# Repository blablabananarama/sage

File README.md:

# Bayleaf: ultra-low-profile wireless split keyboard (reproduction)

This is an open, buildable re-creation of Sebastian Graz's [Bayleaf](https://www.graz.io/articles/bayleaf-wireless-keyboard/): a 60-key (2 × 5×6) ortholinear split keyboard. It uses Kailh PG1316S laptop-style switches, runs ZMK on nice!nano controllers, and sits in a CNC-machined aluminium case 5 mm thick.

> **Provenance.** The original Bayleaf is a one-off prototype and is **not open source**. None of its files are used here. This repository is an independent design built to the published specs (139 × 93 mm per half, 5 mm thick, ~180 g, PG1316S, nice!nano/ZMK, CNC aluminium enclosure, MJF keycaps). Everything else was designed from scratch: board layout, pin mapping, case geometry, keymap and part choices. The PG1316S land pattern comes from Kailh's datasheet (CPG1316S01D02).

| | |
|---|---|
|  |  |
|  |  |
|  |  |
|  | |
|  |  |

**[Interactive case viewer](https://claude.ai/artifact/CuZ9wQ9LTKb2B2hHYhkEA2)**: rotate the five case versions, switch between them and try finishes (source: `docs/viewer/index.html`).

*Renders are generated from the actual STEP files and the routed PCB artwork (`docs/render3d/render.sh`). The case follows the original's MK5 drawing for the plan view and, for the top surface, the shape drawn in the [case sketchpad](https://claude.ai/artifact/11zAxZXfv3bXQXGKN8ovCU) ([data](docs/case-sketchpad-shape.json)): a one-piece silver shell with two flat levels, a 3.2 mm rim around the keys and a 5.0 mm plateau over the controller, joined by soft S-bends, plus a screwed-on black FR4 bottom plate.*

| | Original Bayleaf (published) | This reproduction |
|---|---|---|
| Layout | 60 % ortholinear split | 2 × 5 rows × 6 columns, 17 × 17 mm pitch |
| Size per half | 139 × 93 mm; "tallest part is only 5 mm" | 139.4 × 96.8 mm base. 3.2 mm rim around the keys; 5.0 mm plateau over the controller |
| Weight | 180 g | ~165 g estimated (15 g aluminium shell + 17 g FR4 plate per half) |
| Switches | Kailh PG1316S | Kailh PG1316S, soldered from below with an iron: contacts through castellated half-holes, frame anchors through plated holes (a hotplate is optional) |
| Keycaps | custom MJF prints | stock Kailh PG1316S 1U caps (16 × 16 mm) |
| Controller | nice!nano, ZMK | nice!nano v2 soldered flush, ZMK (BLE split) |
| Battery | "over a month" | 302030 LiPo (~120–150 mAh) per half, deep sleep after 15 min |
| Case | CNC aluminium, raised over the controller | One-piece CNC 6061 shell (key window, roofed controller bay, 7 tapped M2 posts) + 0.8 mm FR4 bottom plate (a copper-free PCB, so the radio gets out) ([notes](docs/case-drawing.md)) |

## What's in here

```
hardware/pcb/generate_pcb.py      the whole PCB as code: placement, nets, outline -> Freerouting -> DRC -> fab files;
                                  also the FR4 bottom plates
hardware/pcb/bayleaf-{left,right}.kicad_pcb   routed KiCad 7 boards (open in KiCad to inspect or edit)
hardware/pcb/lib/bayleaf.pretty/  footprints: PG1316S (castellated, hand-solderable), nice!nano (flush), battery pads
hardware/pcb/fab/{left,right}/    gerbers+drill zip, JLCPCB BOM/CPL, 3D STEP of the board, DRC report
hardware/pcb/fab/plate-{left,right}/  gerbers+drill zip of the FR4 bottom plates
hardware/case/case.py             parametric shell (drafted or straight + chamfer) (CadQuery); out/ has STEP + STL (plate too, for reference)
firmware/                         ZMK shield "bayleaf" + keymap; built by .github/workflows/firmware.yml
docs/BOM.csv                      full bill of materials with prices
docs/ordering.md                  exact fab settings (PCB, PCBA, CNC, parts)
docs/shopping-list.md             every part to buy, with shop links
docs/assembly.md                  step-by-step build guide
docs/schematic.md                 circuit / pin map
docs/case-drawing.md              case dimensions, tapped holes, screws
```

| Left PCB | Right PCB |
|---|---|
|  |  |

## How much does one cost?

These are estimates from September 2026 for a single keyboard, including spares and shipping. The details are in [`docs/BOM.csv`](docs/BOM.csv).

| | USD |
|---|---:|
| PCBs (2 designs × 5 pcs, 0.8 mm, ENIG, castellated holes) | 60 |
| FR4 bottom plates (2 designs × 5 pcs, no copper) | 16 |
| 64 × Kailh PG1316S switches | 64 |
| 60 × PG1316S keycaps | 27 |
| 2 × nice!nano v2 | 50 |
| 2 × LiPo 302030 | 8 |
| Diodes, reset buttons | 2 |
| Foam tape, Kapton tape, bumpons, M2 screws | 17 |
| Shipping (rough) | 35 |
| 2 × CNC aluminium shell (6061, anodised) | 170 |
| **Electronics only** (PCBs, switches, diodes, controllers, batteries, reset buttons) | **≈ $184** |
| **Total with aluminium case** | **≈ $449** |
| **Total with printed nylon case instead** | **≈ $309** |

Optional extras: JLCPCB assembly of the 60 diodes (≈ $35), SMT stencils (≈ $14), and low-temp paste; a small hotplate is optional (≈ $30–120).

Most of the extra units are leftovers you can't avoid: 3 spare PCBs per side at the 5-piece minimum, spare switches, and so on.

## Build it

1. **Order**: follow [docs/ordering.md](docs/ordering.md). Upload the gerber zips, optionally the JLC BOM/CPL, and the case STEP files. Buy switches, caps, 2 nice!nanos and 2 cells.
2. **Firmware**: GitHub Actions builds `bayleaf_left`, `bayleaf_right` and `settings_reset` UF2s on every push. See [firmware/README.md](firmware/README.md).
3. **Assemble**: follow [docs/assembly.md](docs/assembly.md). The rough order is diodes → switches (iron from below: frame anchors, then contacts) → reset button (underside) → nice!nano flush → battery → PCB into the shell → bottom plate + 7 screws.

## Regenerating the design

The committed outputs are all you need to order. To change something (pitch, board size, pin map, case wall), edit the constants at the top of `generate_pcb.py` or `case.py` and run:

```sh
make pcb      # KiCad 7 python (pcbnew) + Freerouting 2.x jar (FREEROUTING_JAR=...)
make case     # CadQuery (shell; imports the FR4 plate for the renders)
make render   # README renders (docs/render3d)
```

The PCB script autoroutes with Freerouting and re-runs until nothing is unrouted. It writes a DRC report next to the gerbers. The committed boards have **0 unconnected pads and 0 electrical DRC errors**; the report only lists cosmetic silkscreen and library-path warnings. The bottom plates are generated in the same run. Freerouting isn't deterministic, so each regeneration produces different (equally valid) traces.

## Status and caveats

* **Not yet built.** The design passes DRC and the case was checked against the board in CAD, but no physical prototype exists yet. Order one set of PCBs before ordering in quantity.
* **Hand-solderable switches.** The PG1316S footprint uses the trick from Mike Holscher's working [mikecinq](https://github.com/mikeholscher/zmk-config-mikecinq): a window in the board under each switch, with the two contacts on plated half-holes at its edge, soldered from below with an iron. On top of that, each of the four frame-anchor pads has a plated hole with a bottom pad, so the anchors can be soldered from below too and no hotplate is needed. The anchor holes are **my addition and untested**: solder one switch first and check it holds before doing the rest. The hotplate route still works on the same board. The footprint is drawn independently from the Kailh land pattern, using his proven contact positions. Order the PCB with *castellated holes*, and print it 1:1 to check against a real switch first.
* The nice!nano is soldered flush, without sockets, to reach 5 mm. Flash and test it **before** soldering it down.
* The LCSC part numbers in the BOM are well-known parts, but check stock before ordering.
* **Case vs. the original.** The plan view comes from the MK5 drawing and the top surface from the sketchpad shape (3.2 / 5.0 mm levels, a square-cornered plateau at x ≥ 96.5, y ≤ 76 mm, 16.5 mm S-bends). The overall depth (4.2 mm border all round) and the keycap height (~4.4 mm) are my estimates. [docs/case-drawing.md](docs/case-drawing.md) marks which numbers come from where.
  * The plateau only covers the back 76 mm of the controller strip, so the PCB is laid out for it: the nice!nano's USB-C faces the **back** wall, the reset button (KMR2) sits beside it, and the cell is a **302030** in front of it (a 302040 would run into the bend).
  * The two posts beside the USB port are moved outward, so they don't land on the nice!nano's pins.
  * Threads are 2 mm deep under the plateau and 1.1 mm under the rim (M2×2 screws there); the drawing's 3 mm ones don't fit under 5 mm.
  * **No power switch.** The cell is wired straight to the nice!nano; ZMK's deep sleep (after 15 min idle, a key press wakes it) keeps the drain to a few µA. To store it for months, unsolder a battery lead.
  * The USB-C opening is a stadium around the receptacle (9.7 × 3.9 mm). The receptacle sits 1.5–2 mm behind the outer wall, so the cable's plug overmold has to fit that opening: slim-overmold cables and magnetic-tip adapters work, bulky plugs won't seat.
  * **Five wall styles** are generated ([comparison from four sides, with cross-sections](docs/img/3d/compare.jpg)). All use the same bottom plate and PCB:
  * default: the drafted walls of the MK5 drawing
  * `bayleaf-shell-*-chamfer`: straight walls with a 0.5 mm × 45° chamfer along the top edge
  * `bayleaf-shell-*-round`: straight walls with the top edge rounded over (R1.5) and a softened key-window edge (R0.8)
  * `bayleaf-shell-*-corner`: straight walls with sharp edges; each outer corner is cut at 45° (2.5 mm legs), and only that corner face gets a R1.5 top and R0.8 bottom round
  * `bayleaf-shell-*-corner2`: the same cut corners only at the back corner by the USB-C and the diagonally opposite front corner; the other two corners keep the R4.2 plan radius ([close comparison](docs/img/3d/compare-corners.jpg))
* **Radio.** The nice!nano sits under the aluminium roof, so the bottom plate is FR4 without any copper: the 2.4 GHz signal leaves downward and through the key window instead of being boxed in. The LiPo sits right at the antenna end of the nice!nano, which costs some range too. The firmware uses +8 dBm TX power. Test range before relying on it; a printed shell is the fallback.
* **Reset button** is on the PCB's underside, in a window of the bottom plate (it stands ~1.1 mm proud of the plate, inside the 1.5 mm feet). JLC's economic assembly is top-side only, so it's hand-soldered.

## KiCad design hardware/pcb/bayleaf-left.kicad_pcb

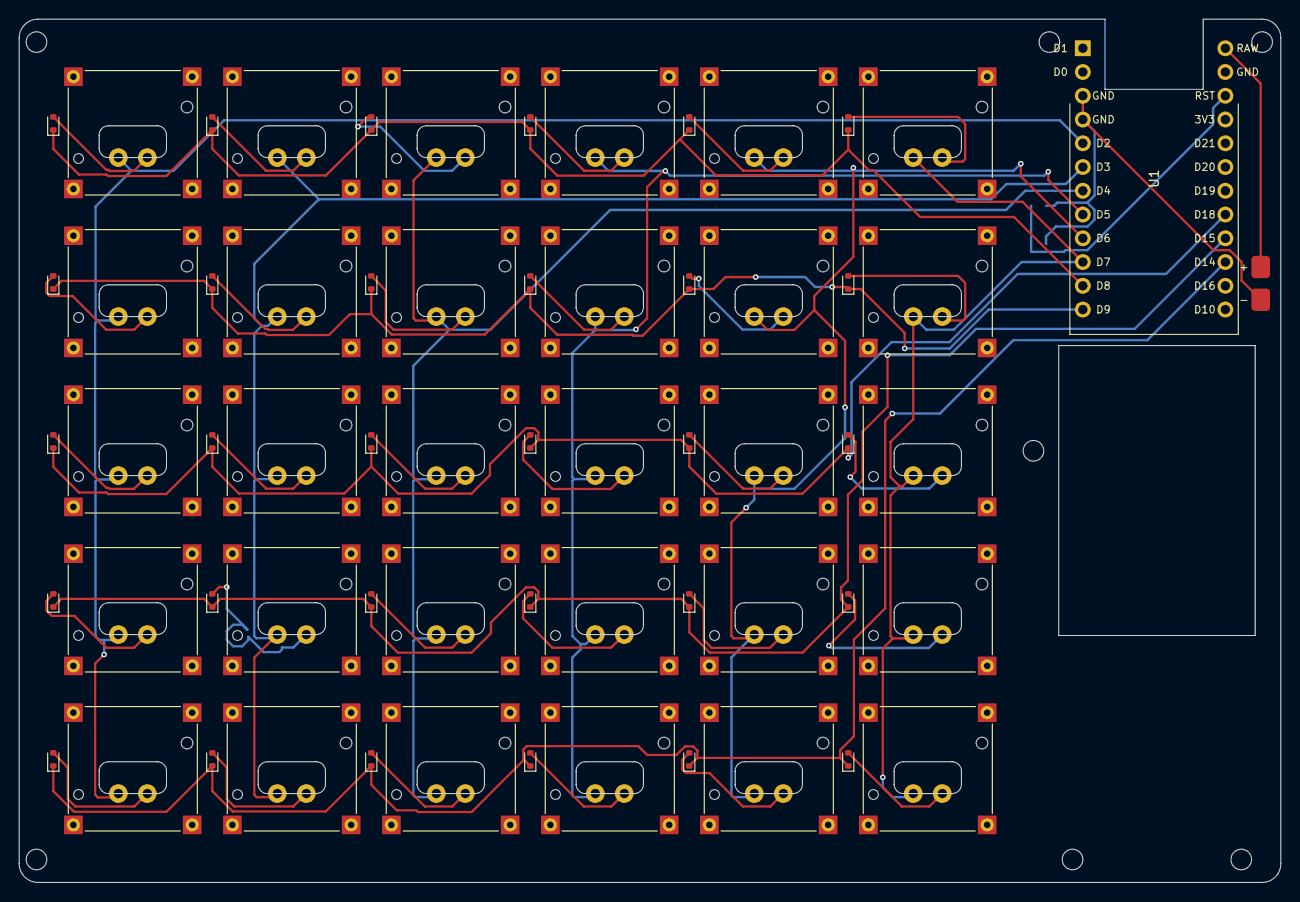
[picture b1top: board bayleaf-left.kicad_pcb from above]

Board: 2 copper layers, 134.9 x 92.3 mm, 70 parts (1 on the bottom side), 44 nets.

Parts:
BT1: LiPo 3.7V; Battery_Pads_Small
D1, D2, D3, D4, D5, D6, D7, D8, D9, D10, D11, D12, D13, D14, D15, D16, D17, D18, D19, D20, D21, D22, D23, D24, D25, D26, D27, D28, D29, D30: 1N4148WT; D_SOD-523
H1, H2, H5, H6, H7: boss 6; MountingHole_2.2mm_M2
H3, H4: boss 4; MountingHole_2.2mm_M2
SW1, SW2, SW3, SW4, SW5, SW6, SW7, SW8, SW9, SW10, SW11, SW12, SW13, SW14, SW15, SW16, SW17, SW18, SW19, SW20, SW21, SW22, SW23, SW24, SW25, SW26, SW27, SW28, SW29, SW30: PG1316S; Kailh_PG1316S_castellated
SW31: KMR211NGLFS; SW_Push_1P1T_NO_CK_KMR2
U1: nice!nano v2; nice_nano_v2_flush

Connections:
COL0: SW1.1, SW7.1, SW13.1, SW19.1, SW25.1, U1.5
COL1: SW2.1, SW8.1, SW14.1, SW20.1, SW26.1, U1.6
COL2: SW3.1, SW9.1, SW15.1, SW21.1, SW27.1, U1.7
COL3: SW4.1, SW10.1, SW16.1, SW22.1, SW28.1, U1.8
COL4: SW5.1, SW11.1, SW17.1, SW23.1, SW29.1, U1.9
COL5: SW6.1, SW12.1, SW18.1, SW24.1, SW30.1, U1.10
GND: BT1.2, SW31.2, U1.3, U1.4
N_SW1: D1.2, SW1.2
N_SW2: D2.2, SW2.2
N_SW3: D3.2, SW3.2
N_SW4: D4.2, SW4.2
N_SW5: D5.2, SW5.2
N_SW6: D6.2, SW6.2
N_SW7: D7.2, SW7.2
N_SW8: D8.2, SW8.2
N_SW9: D9.2, SW9.2
N_SW10: D10.2, SW10.2
N_SW11: D11.2, SW11.2
N_SW12: D12.2, SW12.2
N_SW13: D13.2, SW13.2
N_SW14: D14.2, SW14.2
N_SW15: D15.2, SW15.2
N_SW16: D16.2, SW16.2
N_SW17: D17.2, SW17.2
N_SW18: D18.2, SW18.2
N_SW19: D19.2, SW19.2
N_SW20: D20.2, SW20.2
N_SW21: D21.2, SW21.2
N_SW22: D22.2, SW22.2
N_SW23: D23.2, SW23.2
N_SW24: D24.2, SW24.2
N_SW25: D25.2, SW25.2
N_SW26: D26.2, SW26.2
N_SW27: D27.2, SW27.2
N_SW28: D28.2, SW28.2
N_SW29: D29.2, SW29.2
N_SW30: D30.2, SW30.2
RAW: BT1.1, U1.13
ROW0: D1.1, D2.1, D3.1, D4.1, D5.1, D6.1, U1.11
ROW1: D7.1, D8.1, D9.1, D10.1, D11.1, D12.1, U1.12
ROW2: D13.1, D14.1, D15.1, D16.1, D17.1, D18.1, U1.20
ROW3: D19.1, D20.1, D21.1, D22.1, D23.1, D24.1, U1.21
ROW4: D25.1, D26.1, D27.1, D28.1, D29.1, D30.1, U1.22
RST: SW31.1, U1.15
